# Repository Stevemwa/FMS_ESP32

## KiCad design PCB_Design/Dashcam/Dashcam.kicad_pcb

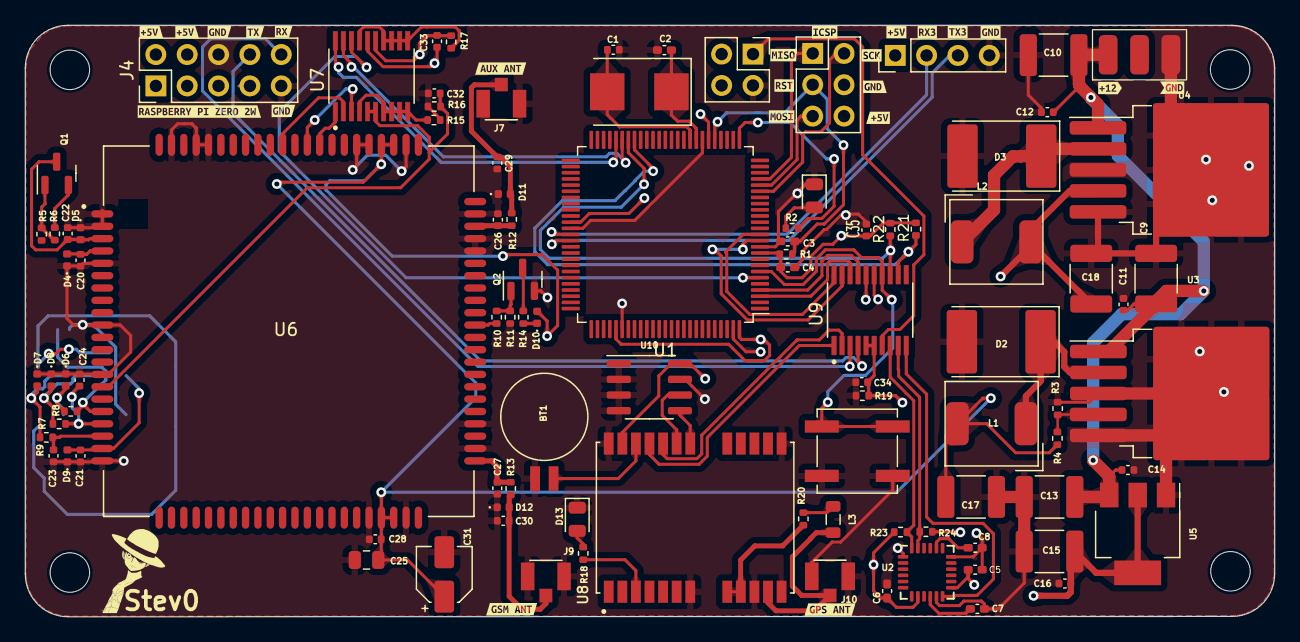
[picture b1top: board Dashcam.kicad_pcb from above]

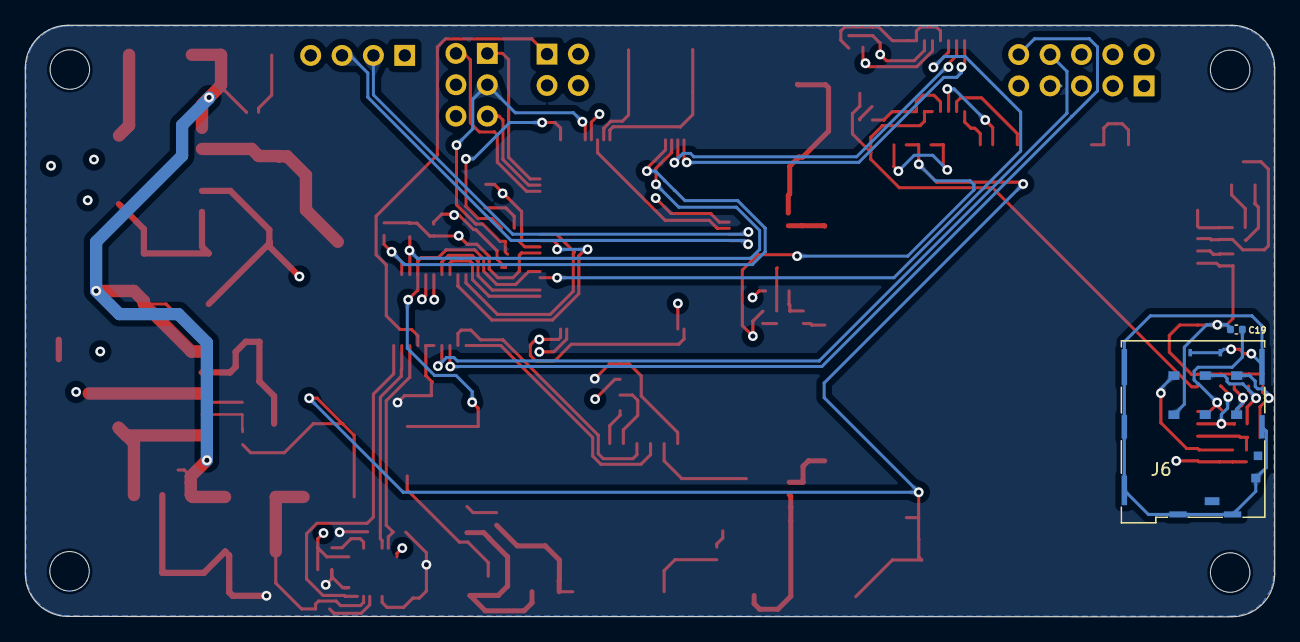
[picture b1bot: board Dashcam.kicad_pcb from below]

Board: 4 copper layers, 101.2 x 47.9 mm, 129 parts (2 on the bottom side), 71 nets.

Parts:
BT1: Battery_Cell; BatteryHolder_Seiko_MS621F
C1, C19, C23, C24: 22pF; C_0402_1005Metric
C2, C3: 22pF; C_0402_1005Metric_Pad0.74x0.62mm_HandSolder
C4: 100nF; C_0402_1005Metric_Pad0.74x0.62mm_HandSolder
C5, C7: 0.1uF; C_0402_1005Metric_Pad0.74x0.62mm_HandSolder
C6: 10nF; C_0402_1005Metric_Pad0.74x0.62mm_HandSolder
C8: 2.2uF; C_0402_1005Metric_Pad0.74x0.62mm_HandSolder
C9, C10, C13, C15, C17, C18: 220uF; C_1812_4532Metric
C11, C12, C14, C16, C20, C21, C22, C32, C33, C34, C35: 100nF; C_0402_1005Metric
C25: 100uF; C_0805_2012Metric
C26, C27, C29, C30: NC; C_0402_1005Metric
C28: 1uF; C_0402_1005Metric
C31: 100uF; CP_Elec_4x3
D1, D13: LED; LED_0805_2012Metric
D2, D3: B320; D_3220_8050Metric
D4, D5, D11, D12: D_TVS; D_0402_1005Metric
D6, D7, D8, D9: TVS; D_0402_1005Metric
D10: LED; LED_0402_1005Metric
H1, H2, H3, H4, H5, H6: MountingHole; MountingHole_3.2mm_M3
J1: Conn_02x03_Counter_Clockwise; PinHeader_2x03_P2.54mm_Vertical
J2: Conn_01x04; PinHeader_1x04_P2.54mm_Vertical
J3: Conn_01x03; 3pin_solder
J4: Conn_02x05_Odd_Even; PinHeader_2x05_P2.54mm_Vertical
J5: Conn_02x02_Top_Bottom; PinHeader_2x02_P2.54mm_Vertical
J6: JAE_SIM_Card_SF72S006
J7, J9, J10: U.FL-R-SMT_01_; HRS_U.FL-R-SMT_01_
L1, L2: 330uH; L_AVX_LMLP07A7
L3: 27nH; L_0805_2012Metric
Q1, Q2: BC818; SOT-23
R1, R2, R3, R4, R5, R6, R10, R11, R21, R22: 10k; R_0402_1005Metric
R7, R8, R9: 22R; R_0402_1005Metric
R12, R13: 0R; R_0402_1005Metric
R14: 300R; R_0402_1005Metric
R15, R16, R17, R19: 47k; R_0402_1005Metric
R18: 1k; R_0402_1005Metric
R20: 10R; R_0402_1005Metric
R23, R24: 4.7k; R_0402_1005Metric
SW1: SW_Push; SW_SPST_B3SL-1002P
Stev0: LOGO; Luffy6by6
U1: ATmega2560-16A; TQFP-100_14x14mm_P0.5mm
U2: MPU-6050; InvenSense_QFN-24_4x4mm_P0.5mm
U3: LM2596S-ADJ; TO-263-5_TabPin3
U4: LM2596S-5; TO-263-5_TabPin3
U5: AMS1117-3.3; SOT-223-3_TabPin2
U6: SIM7600E-H; IC_SIM7600E-H
U7, U9: TXB0108DQSR; SOP65P640X120-20N
U8: NEO-6M-GPS; XCVR_NEO-6M-GPS
U10: 24LC32; SOIC-8_3.9x4.9mm_P1.27mm
Y1: 16MHz; Crystal_SMD_7050-2Pin_7.0x5.0mm
kibuzzard-65B8E8C6: G***; kibuzzard-65B8E8C6
kibuzzard-65B8E8EC: G***; kibuzzard-65B8E8EC
kibuzzard-65B8E927: G***; kibuzzard-65B8E927
kibuzzard-65B8E947: G***; kibuzzard-65B8E947
kibuzzard-65B8E966: G***; kibuzzard-65B8E966
kibuzzard-65B8EF0A: G***; kibuzzard-65B8EF0A
kibuzzard-65B8EF6A: G***; kibuzzard-65B8EF6A
kibuzzard-65B8EF7A: G***; kibuzzard-65B8EF7A
kibuzzard-65B8EF8E: G***; kibuzzard-65B8EF8E
kibuzzard-65B8EF27: G***; kibuzzard-65B8EF27
kibuzzard-65B8EF32: G***; kibuzzard-65B8EF32
kibuzzard-65B8EF58: G***; kibuzzard-65B8EF58
kibuzzard-65B8F0B4: G***; kibuzzard-65B8F0B4
kibuzzard-65B8F6F0, kibuzzard-65B8F6F0#2: G***; kibuzzard-65B8F6F0
kibuzzard-65B8F7D9: G***; kibuzzard-65B8F7D9
kibuzzard-65B8F7E7: G***; kibuzzard-65B8F7E7
kibuzzard-65B8F7F5: G***; kibuzzard-65B8F7F5
kibuzzard-65B8F71B, kibuzzard-65B8F71B#2: G***; kibuzzard-65B8F71B
kibuzzard-65B8F739: G***; kibuzzard-65B8F739
kibuzzard-65B8F746: G***; kibuzzard-65B8F746
kibuzzard-65B8F803: G***; kibuzzard-65B8F803

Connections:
3V8: C17.2, C25.1, C28.1, C31.1, D10.2 (A), L1.2, R4.2, U6.38 (VBAT), U6.39 (VBAT), U6.62 (VBAT), U6.63 (VBAT)
+1V8: C32.2, R16.2, U6.15 (VDD_1V8), U7.5 (VCCA), U7.6 (OE)
+3V3: C5.2, C6.2, C15.2, C16.2, C34.2, R19.2, R23.1, R24.1, U2.8 (VLOGIC), U2.13 (VDD), U5.2 (VO), U8.23 (VCC), U9.5 (VCCA), U9.6 (OE), U10.8 (VCC)
+5V: C4.2, C18.2, C33.1, C35.1, J1.6, J2.1, J4.2, J4.4, L2.2, R1.1, R21.1, R22.1, U1.10 (VCC), U1.31 (VCC), U1.61 (VCC), U1.80 (VCC), U1.100 (AVCC), U4.4 (FB), U7.16 (VCCB), U9.16 (VCCB)
+12V: C9.2, C10.2, C11.2, C12.2, C13.2, C14.2, J3.1, U3.1 (VIN), U4.1 (VIN), U5.3 (VI)
GND: BT1.2 (-), C1.1, C2.1, C3.2, C4.1, C5.1, C6.1, C7.1, C8.1, C9.1, C10.1, C11.1, C12.1, C13.1, C14.1, C15.1, C16.1, C17.1, C18.1, C19.2, C20.2, C21.1, C22.2, C23.2, C24.2, C25.2, C26.2, C27.2, C28.2, C29.2, C30.2, C31.2, C32.1, C33.2, C34.1, C35.2, D1.1 (K), D2.2 (A), D3.2 (A), D4.1 (A1), D5.1 (A1), D6.1 (A1), D7.1 (A1), D8.1 (A1), D9.1 (A1), D11.1 (A1), D12.1 (A1), D13.1 (K), J1.4, J2.4, J3.3, J4.6, J4.9, J5.2, J6.C5 (GND), J7.1 (GND), J7.2 (GND), J9.1 (GND), J9.2 (GND), J10.1 (GND), J10.2 (GND), Q2.2 (E), R3.1, R11.2, R15.1, R16.1, R17.2, R19.1, SW1.1, U1.11 (GND), U1.32 (GND), U1.62 (GND), U1.81 (GND), U1.99 (GND), U2.1 (CLKIN), U2.11 (FSYNC), U2.18 (GND), U3.3 (GND), U3.5 (~ON/OFF), U4.3 (GND), U4.5 (~ON/OFF), U5.1 (GND), U6.1 (GND), U6.2 (GND), U6.5 (GND), U6.10 (GND), U6.14 (GND), U6.37 (GND), U6.40 (GND), U6.41 (GND), U6.43 (GND), U6.57 (GND), U6.58 (GND), U6.60 (GND), U6.61 (GND), U6.64 (GND), U6.65 (GND), U6.77 (GND), U6.78 (GND), U6.80 (GND), U6.81 (GND), U7.15 (GND), U8.7 (VDDUSB), U8.10 (GND), U8.12 (GND), U8.13 (GND), U8.24 (GND), U9.15 (GND), U10.1 (A0), U10.2 (A1), U10.3 (A2), U10.4 (GND), U10.7 (WP)
INT4: U1.6 (PE4), U7.18 (B3)
INT5: SW1.2, U1.7 (PE5), U9.14 (B5)
LED_ATmega: R2.2, U1.26 (PB7)
MISO: J1.1, U1.22 (PB3)
MOSI: J1.5, U1.21 (PB2)
MPU6050-INT: U2.12 (INT), U9.10 (A8)
NEO-RX: U8.21 (RXD1), U9.1 (A1)
NEO-SCL: U8.19 (SCL2), U10.6 (SCL)
NEO-SDA: U8.18 (SDA2), U10.5 (SDA)
NEO-TX: U8.20 (TXD1), U9.2 (A2)
unnamed: BT1.1 (+), U8.22 (V_BCKP)
unnamed: D1.2 (A), R2.1
unnamed: D2.1 (K), L1.1, U3.2 (OUT)
unnamed: D3.1 (K), L2.1, U4.2 (OUT)
unnamed: C20.1, D4.2 (A2), U6.4 (RESET)
unnamed: C22.1, D5.2 (A2), Q1.3 (C), U6.3 (PWRKEY)
unnamed: D6.2 (A2), J6.C7 (I/O), R8.2
unnamed: D7.2 (A2), J6.C3 (CLK), R9.2
unnamed: D8.2 (A2), J6.C2 (RST), R7.2
unnamed: D10.1 (K), R14.2
unnamed: C29.1, D11.2 (A2), J7.3 (SIG), R12.2
unnamed: C30.1, D12.2 (A2), J9.3 (SIG), R13.2
unnamed: D13.2 (A), R18.1
unnamed: L3.1, R20.1
unnamed: Q1.1 (B), R5.2, R6.1
unnamed: Q1.2 (E), R6.2
unnamed: Q2.1 (B), R10.2, R11.1
unnamed: Q2.3 (C), R14.1
unnamed: C1.2, U1.34 (XTAL1), Y1.2
unnamed: C2.2, U1.33 (XTAL2), Y1.1
unnamed: C8.2, U2.20 (CPOUT)
unnamed: C7.2, U2.10 (REGOUT)
unnamed: R3.2, R4.1, U3.4 (FB)
unnamed: C26.1, R12.1, U6.59 (AUX_ANT)
unnamed: C27.1, R13.1, U6.82 (MAIN_ANT)
unnamed: R10.1, U6.51 (NETLIGHT)
unnamed: R15.2, U7.4 (A4), U7.7 (A5), U7.8 (A6), U7.9 (A7), U7.10 (A8)
unnamed: R17.1, U7.11 (B8), U7.12 (B7), U7.13 (B6), U7.14 (B5), U7.17 (B4)
unnamed: R20.2, U8.8 (RSVD_8), U8.9 (VCC_RF)
unnamed: R18.2, U8.3 (TIMEPULSE)
PI-INT: J5.1, U9.7 (A5)
PI-RX: J4.10, U9.3 (A3)
PI-TX: J4.8, U9.4 (A4)
RESET: C3.1, J1.3, R1.2, U1.30 (~RESET)
RF-IN: J10.3 (SIG), L3.2, U8.11 (RF_IN)
RX3: J2.2, U1.63 (PJ0)
RX-GPS: U1.13 (PH1), U9.20 (B1)
RX-PI: U1.3 (PE1), U9.18 (B3)
RX-SIM: U1.46 (PD3), U7.20 (B1)
SCK: J1.2, U1.20 (PB1)
SCL: R21.2, U1.43 (PD0), U9.12 (B7)
SCL-MPU6050: R24.2, U2.23 (SCL), U9.9 (A7)
SDA: R22.2, U1.44 (PD1), U9.13 (B6)
SDA-MPU6050: R23.2, U2.24 (SDA), U9.8 (A6)
SIM-RX: U6.68 (RXD), U7.1 (A1)
SIM-TXD: U6.71 (TXD), U7.2 (A2)
SIMI-INTERUPT: U6.69 (RI), U7.3 (A3)
TX3: J2.3, U1.64 (PJ1)
TX-GPS: U1.12 (PH0), U9.19 (B2)
TX-PI: U1.4 (PE2), U9.17 (B4)
TX-SIM: U1.45 (PD2), U7.19 (B2)
USIM-CLK: C23.1, R9.1, U6.19 (USIM_CLK)
USIM-DATA: C19.1, R8.1, U6.17 (USIM_DATA)
USIM-RST: C24.1, R7.1, U6.18 (USIM_RST)
USIM-VDD: C21.2, D9.2 (A2), J6.C1 (VCC), U6.20 (USIM_VDD)
